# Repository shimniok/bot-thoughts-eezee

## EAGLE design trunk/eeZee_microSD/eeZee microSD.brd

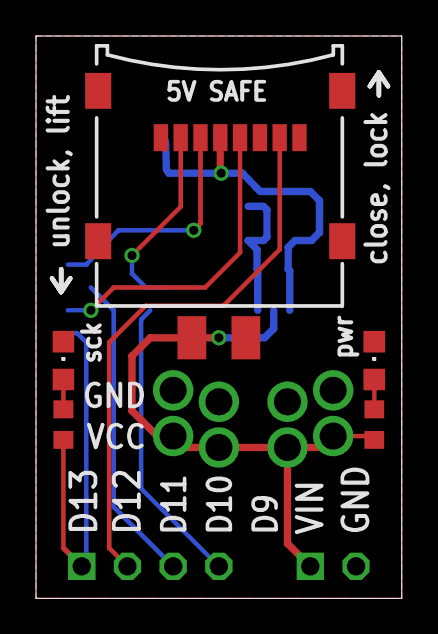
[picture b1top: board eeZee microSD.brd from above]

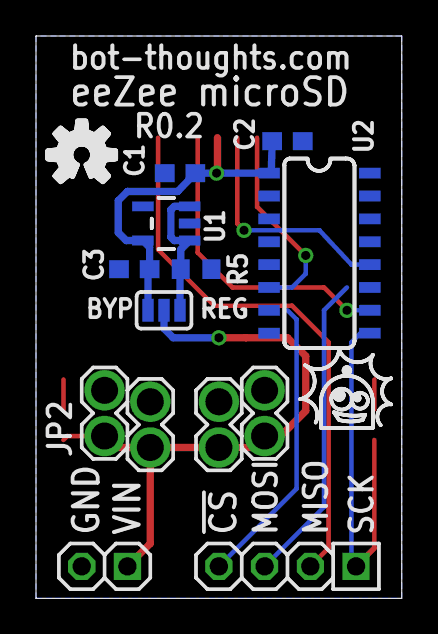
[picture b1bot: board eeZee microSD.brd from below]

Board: 2 copper layers, 20.3 x 31.2 mm, 19 parts (13 on the bottom side), 13 nets.

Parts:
C1: 1uF; C0603
C2, C3: 0.1uF; C0603
C4: 10uF; SMC_B
JP1: 1X02-S
JP2, JP3, JP4, JP5: PWR; BIGPIN-2
JP6: 1X04-S
LED1, LED2: CHIPLED_0805
R1, R2: 1K; R0603
R5: 10K; R0603
REG: BYP; SJ_3
U1: MCP1824S; SOT23-5
U2: 74HC4050; SO016
U$1: MICROSD_TFLASH; TFLASH_CP-0000-086

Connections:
!CS_HV: JP6.4, U2.7
!SS: U2.6, U$1.CS
GND: C1.2, C2.2, C3.2, C4.-, JP1.2, JP2.P$2, JP3.P$2, JP4.P$2, JP5.P$2, LED1.C, LED2.C, R5.1, U1.2, U2.3, U2.5, U2.8, U2.14, U$1.GND, U$1.SHIELD1, U$1.SHIELD2, U$1.SHIELD3, U$1.SHIELD4
MISO: JP6.2, U$1.DO
MOSI: U2.12, U$1.DI
MOSI_HV: JP6.3, U2.11
unnamed: LED2.A, R2.1
unnamed: LED1.A, R1.1
SCK: U2.10, U$1.SCLK
SCK_HV: JP6.1, R1.2, U2.9
VBOARD: C4.+, JP1.1, JP2.P$1, JP3.P$1, JP4.P$1, JP5.P$1, R2.2, REG.2
VCC: C1.1, C2.1, C3.1, REG.1, U1.5, U2.1, U$1.VDD
VREGIN: R5.2, REG.3, U1.1, U1.3

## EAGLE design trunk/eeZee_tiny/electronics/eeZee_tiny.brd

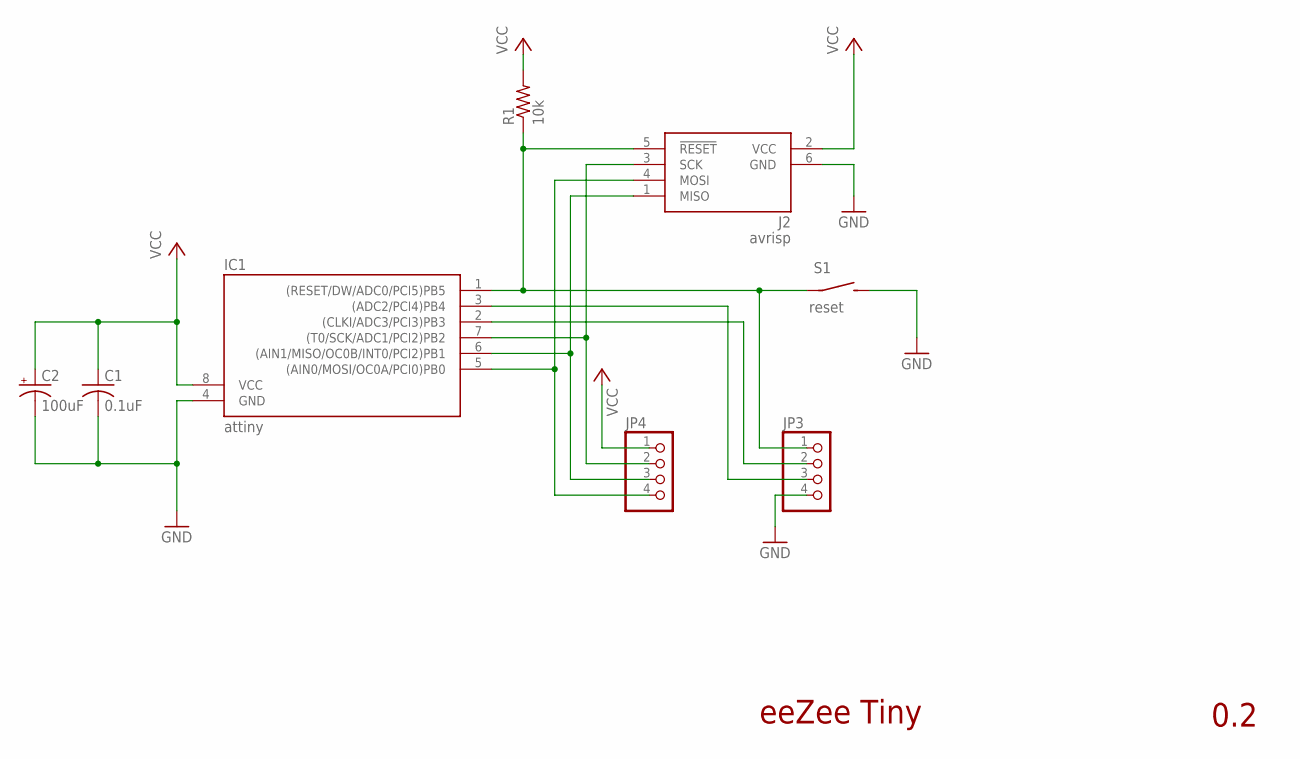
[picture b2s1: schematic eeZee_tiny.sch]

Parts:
C1: 0.1uF; C0603; PARTNO 0603YC104KAT2A
C2: 100uF; SMC_B; PARTNO F930J107MBA
IC1: attiny; DIL08; PARTNO A08-LC-TT-R
J2: avrisp; CON6P2R
JP3, JP4: PINHD-1X04_2.54-S; 1X04-S
R1: 10k; R0603; PARTNO ERJ-3GEYJ103V
S1: reset; 6MMTACTILE_RECT

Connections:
!RESET: IC1.1 ((RESET/DW/ADC0/PCI5)PB5), J2.5 (!RESET), JP3.1, R1.1, S1.P$1
GND: C1.2, C2.-, IC1.4 (GND), J2.6 (GND), JP3.4, S1.P$2 (S)
MISO: IC1.6 ((AIN1/MISO/OC0B/INT0/PCI2)PB1), J2.1 (MISO), JP4.3
MOSI: IC1.5 ((AIN0/MOSI/OC0A/PCI0)PB0), J2.4 (MOSI), JP4.4
unnamed: IC1.2 ((CLKI/ADC3/PCI3)PB3), JP3.2
unnamed: IC1.3 ((ADC2/PCI4)PB4), JP3.3
SCK: IC1.7 ((T0/SCK/ADC1/PCI2)PB2), J2.3 (SCK), JP4.2
VCC: C1.1, C2.+, IC1.8 (VCC), J2.2 (VCC), JP4.1, R1.2

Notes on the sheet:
eeZee Tiny
0.2

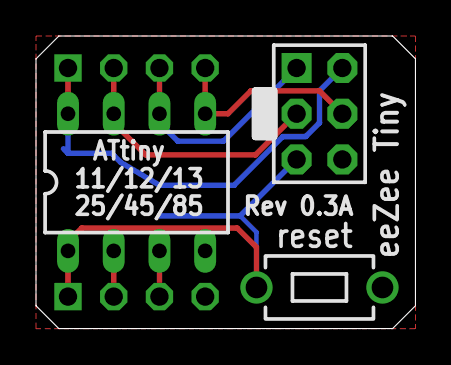
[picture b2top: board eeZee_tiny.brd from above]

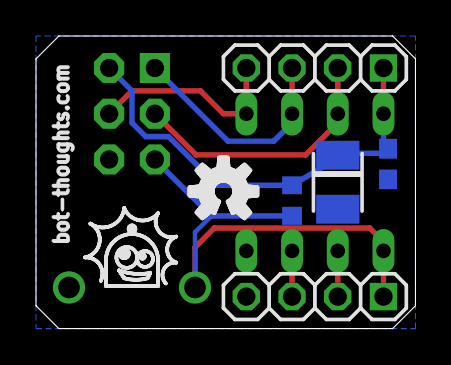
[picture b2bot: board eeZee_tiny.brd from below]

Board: 2 copper layers, 21.1 x 16.3 mm, 8 parts (5 on the bottom side), 8 nets.

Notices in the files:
parts and their libraries:
SparkFun: Licensing: CC v3.0 Share-Alike You are welcome to use this library for commercial purposes.
